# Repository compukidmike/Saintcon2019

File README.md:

# Saintcon 2019 Enigma Badge

## About the Badge
There is a writeup available at https://mkfactor.com/?p=100

There is also a video of my badge talk at Saintcon https://www.youtube.com/watch?v=MAhJ2W_oN14

## Completing the Badge Challenge
Since you probably don't have 26 badges and a Hut 6 "teleprinter" at your house, it will be difficult to complete the challenge. I have created a modified version of the badge firmware that will allow you to complete the challenge at home! You'll need to complete the steps for reprogramming your badge below. Once that's done, grab the Saintcon2019BadgeChallenge.pdf file from this repository. It has all the intercepted messages for you to decode. Be sure to decode them in order! Your badge should say "LEVELED UP" after successfully decoding a message. Good luck! If you get stuck, feel free to reach out on the SaintComms slack, or via twitter @compukidmike or even email compukidmike @ gmail.

## Reprogramming your badge
Note: This will completely erase the memory on your badge. Any progress in the challenge, as well as custom messages will be lost.

You will need the STM32CubeProgrammer software from https://www.st.com/en/development-tools/stm32cubeprog.html to reprogram your badge. It's cross-platform, though I've only tested it on Windows 10. Unfortunately ST requires you to create a login to download software :(

You'll also need the 2 hex files called Saintcon2019.hex and fpga.hex from this repository as well as a micro USB cable and one of the plugboard jumper wires from your badge.

Programming Steps:
1. Turn off the badge.
2. Connect the 2 TEST pins on your badge using the jumper (On the bottom-right side of your badge). If you haven't soldered that connector, you can put the jumper in from the back and hold it.
3. Connect the badge to your computer using a micro USB cable.
4. Turn on the badge. It will boot into DFU (Device Firmware Upgrade) mode.
5. From the STM32CubeProgrammer application, select USB from the drop-down menu at the top-right.
6. If you don't see anything next to "Serial number", click the little refresh button.
7. Click the green "Connect" button in the top-right corner. It should now say "Connected" above that button.
8. Click the Eraser button on the bottom-left corner (right above the question mark) and click OK to erase the badge memory. This is required for the new program to run correctly as there were many changes made to the way the internal EEPROM is organized.
9. Now click the "+" tab next to Device Memory and select "Open file". Choose one of the hex files you downloaded earlier. Now do the same for the other hex file.
10. With one of the hex file tabs selected, click the blue Download button. This will load the file onto your badge. Now do the same for the other hex file tab.
11. Remove the jumper and turn it off and back on. The first time you turn it on, it will go into a testing mode, where all the LEDs are turned on white. This is normal. Simply press each keyboard button until all the lampboard lights are off. It will say "TEST DONE". Turn it off and back on, and you are finished programming your badge. Enjoy!

## Editing Badge Code
The badge code can be found in the Firmware folder. It was written using the STM32CubeIDE. It's cross-platform and works reasonably well. You'll need an ST-Link V2 USB adapter to program and debug your badge. They can be had for ~$10 from Amazon or even less from Aliexpress if you're willing to wait for shipping.
The IDE can be downloaded from ST here: https://www.st.com/en/development-tools/stm32cubeide.html

The FPGA code was written using Icestudio https://icestudio.io/ It's a cross-platform IDE for Lattice ICE40 FPGAs

The FPGA code is in SaintconFPGA.ice

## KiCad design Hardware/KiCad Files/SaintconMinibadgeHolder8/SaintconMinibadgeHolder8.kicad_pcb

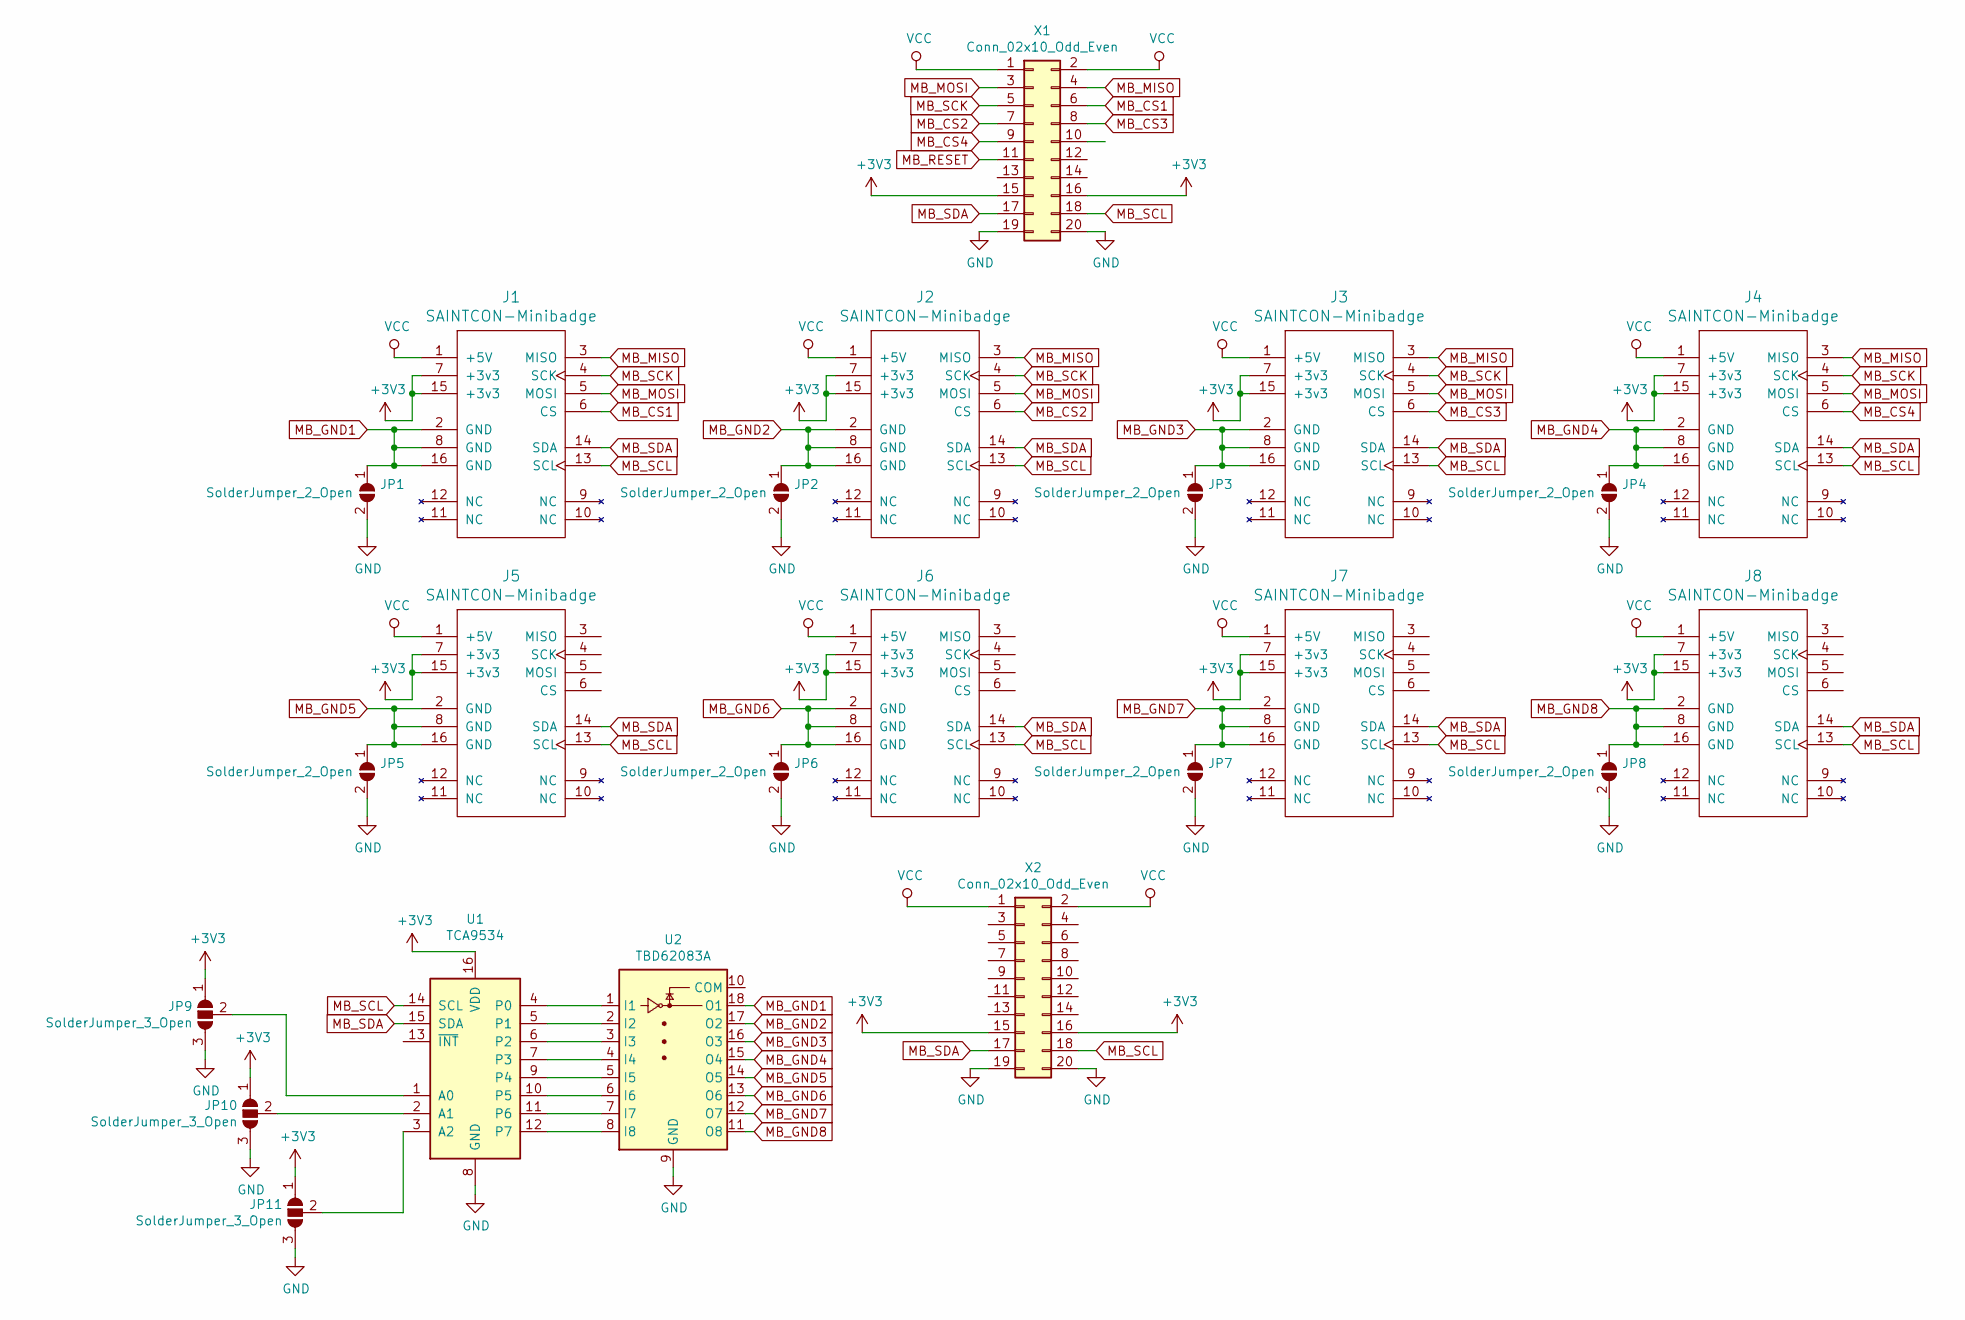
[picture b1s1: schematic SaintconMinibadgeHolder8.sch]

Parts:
J1, J2, J3, J4, J5, J6, J7, J8: SAINTCON-Minibadge; SAINTCON-Minibadge-Shiny
JP1, JP2, JP3, JP4, JP5, JP6, JP7, JP8: SolderJumper_2_Open; PAD-JUMPER-2-NO_YES_SILK
JP9, JP10, JP11: SolderJumper_3_Open; PAD-JUMPER-3-NO_YES_SILK
U1: TCA9534; SOIC-16W_7.5x10.3mm_Pitch1.27mm
U2: TBD62083A; SOIC-18W_7.5x11.6mm_Pitch1.27mm
X1, X2: Conn_02x10_Odd_Even; Pin_Header_Straight_2x10_Pitch2.54mm

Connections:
+3V3: J1.7 (+3v3), J1.15 (+3v3), J2.7 (+3v3), J2.15 (+3v3), J3.7 (+3v3), J3.15 (+3v3), J4.7 (+3v3), J4.15 (+3v3), J5.7 (+3v3), J5.15 (+3v3), J6.7 (+3v3), J6.15 (+3v3), J7.7 (+3v3), J7.15 (+3v3), J8.7 (+3v3), J8.15 (+3v3), JP9.1 (A), JP10.1 (A), JP11.1 (A), U1.16 (VDD), X1.15, X1.16, X2.15, X2.16
GND: JP1.2 (B), JP2.2 (B), JP3.2 (B), JP4.2 (B), JP5.2 (B), JP6.2 (B), JP7.2 (B), JP8.2 (B), JP9.3 (B), JP10.3 (B), JP11.3 (B), U1.8 (GND), U2.9 (GND), X1.19, X1.20, X2.19, X2.20
MB_CS1: J1.6 (CS), X1.6
MB_CS2: J2.6 (CS), X1.7
MB_CS3: J3.6 (CS), X1.8
MB_CS4: J4.6 (CS), X1.9
MB_GND1: J1.2 (GND), J1.8 (GND), J1.16 (GND), JP1.1 (A), U2.18 (O1)
MB_GND2: J2.2 (GND), J2.8 (GND), J2.16 (GND), JP2.1 (A), U2.17 (O2)
MB_GND3: J3.2 (GND), J3.8 (GND), J3.16 (GND), JP3.1 (A), U2.16 (O3)
MB_GND4: J4.2 (GND), J4.8 (GND), J4.16 (GND), JP4.1 (A), U2.15 (O4)
MB_GND5: J5.2 (GND), J5.8 (GND), J5.16 (GND), JP5.1 (A), U2.14 (O5)
MB_GND6: J6.2 (GND), J6.8 (GND), J6.16 (GND), JP6.1 (A), U2.13 (O6)
MB_GND7: J7.2 (GND), J7.8 (GND), J7.16 (GND), JP7.1 (A), U2.12 (O7)
MB_GND8: J8.2 (GND), J8.8 (GND), J8.16 (GND), JP8.1 (A), U2.11 (O8)
MB_MISO: J1.3 (MISO), J2.3 (MISO), J3.3 (MISO), J4.3 (MISO), X1.4
MB_MOSI: J1.5 (MOSI), J2.5 (MOSI), J3.5 (MOSI), J4.5 (MOSI), X1.3
MB_RESET: X1.11
MB_SCK: J1.4 (SCK), J2.4 (SCK), J3.4 (SCK), J4.4 (SCK), X1.5
MB_SCL: J1.13 (SCL), J2.13 (SCL), J3.13 (SCL), J4.13 (SCL), J5.13 (SCL), J6.13 (SCL), J7.13 (SCL), J8.13 (SCL), U1.14 (SCL), X1.18, X2.18
MB_SDA: J1.14 (SDA), J2.14 (SDA), J3.14 (SDA), J4.14 (SDA), J5.14 (SDA), J6.14 (SDA), J7.14 (SDA), J8.14 (SDA), U1.15 (SDA), X1.17, X2.17
unnamed: JP9.2 (C), U1.1 (A0)
unnamed: JP10.2 (C), U1.2 (A1)
unnamed: JP11.2 (C), U1.3 (A2)
unnamed: U1.4 (P0), U2.1 (I1)
unnamed: U1.5 (P1), U2.2 (I2)
unnamed: U1.6 (P2), U2.3 (I3)
unnamed: U1.7 (P3), U2.4 (I4)
unnamed: U1.9 (P4), U2.5 (I5)
unnamed: U1.10 (P5), U2.6 (I6)
unnamed: U1.11 (P6), U2.7 (I7)
unnamed: U1.12 (P7), U2.8 (I8)
VCC: J1.1 (+5V), J2.1 (+5V), J3.1 (+5V), J4.1 (+5V), J5.1 (+5V), J6.1 (+5V), J7.1 (+5V), J8.1 (+5V), X1.1, X1.2, X2.1, X2.2

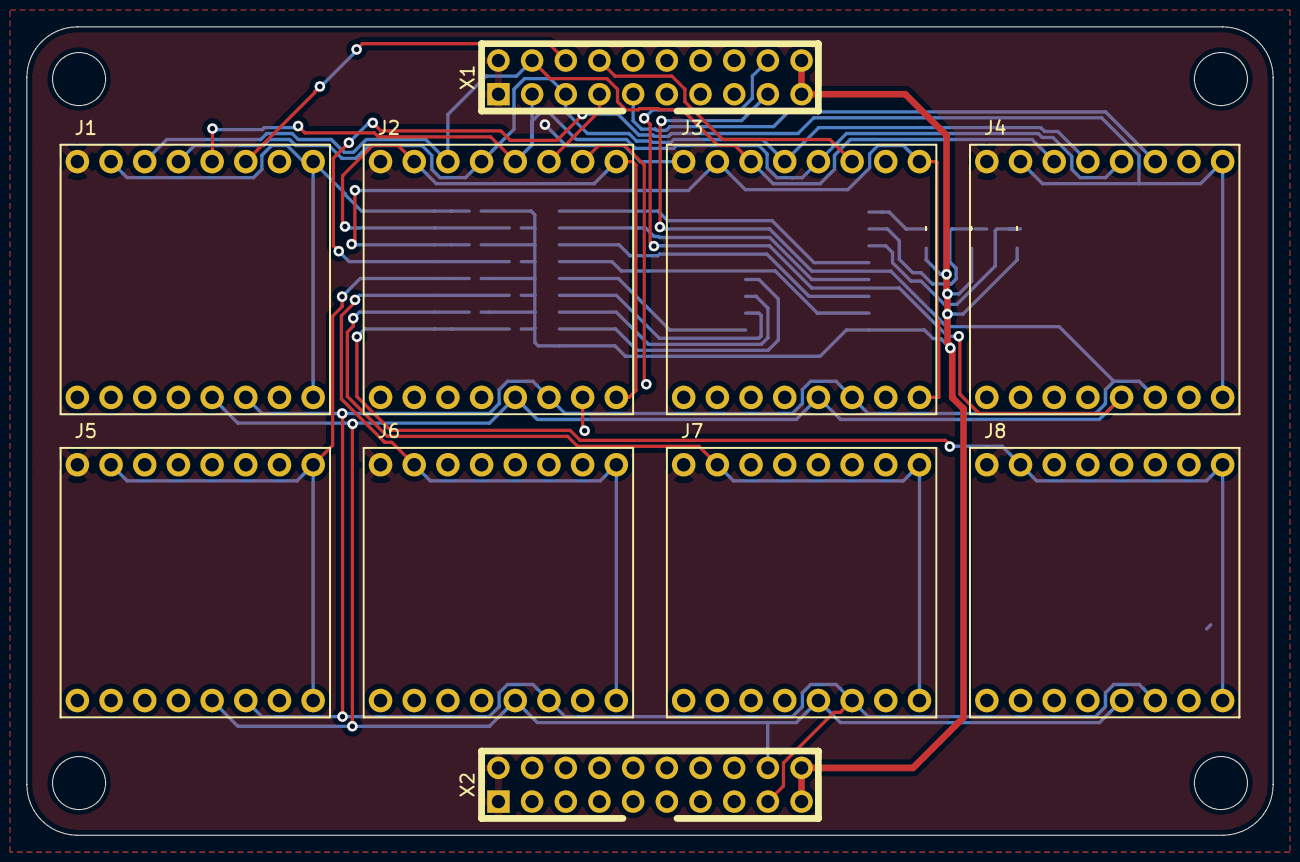
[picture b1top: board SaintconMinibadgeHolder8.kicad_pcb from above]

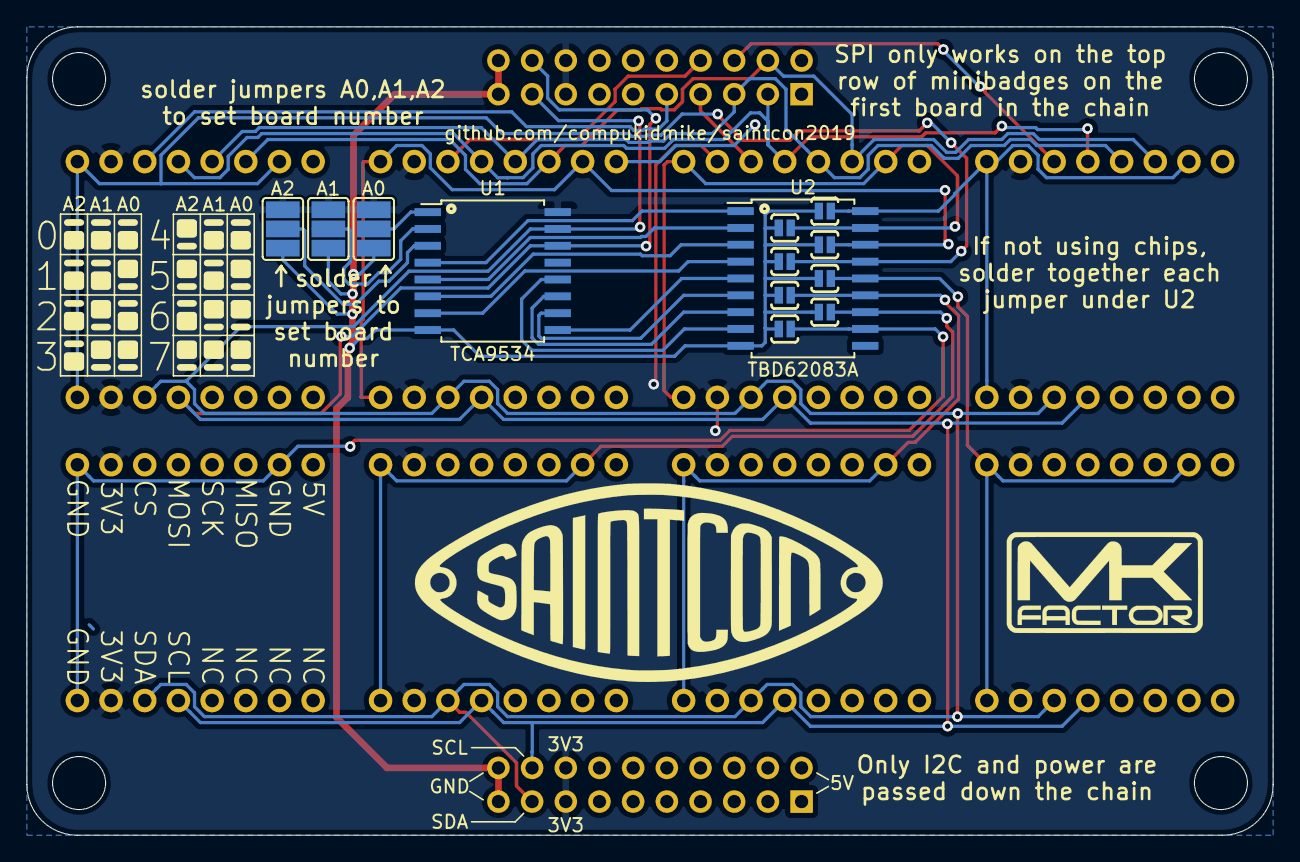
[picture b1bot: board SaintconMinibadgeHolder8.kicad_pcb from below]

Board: 2 copper layers, 94.0 x 61.0 mm, 24 parts (14 on the bottom side), 31 nets.

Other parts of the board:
Ref**: Val**; drawing

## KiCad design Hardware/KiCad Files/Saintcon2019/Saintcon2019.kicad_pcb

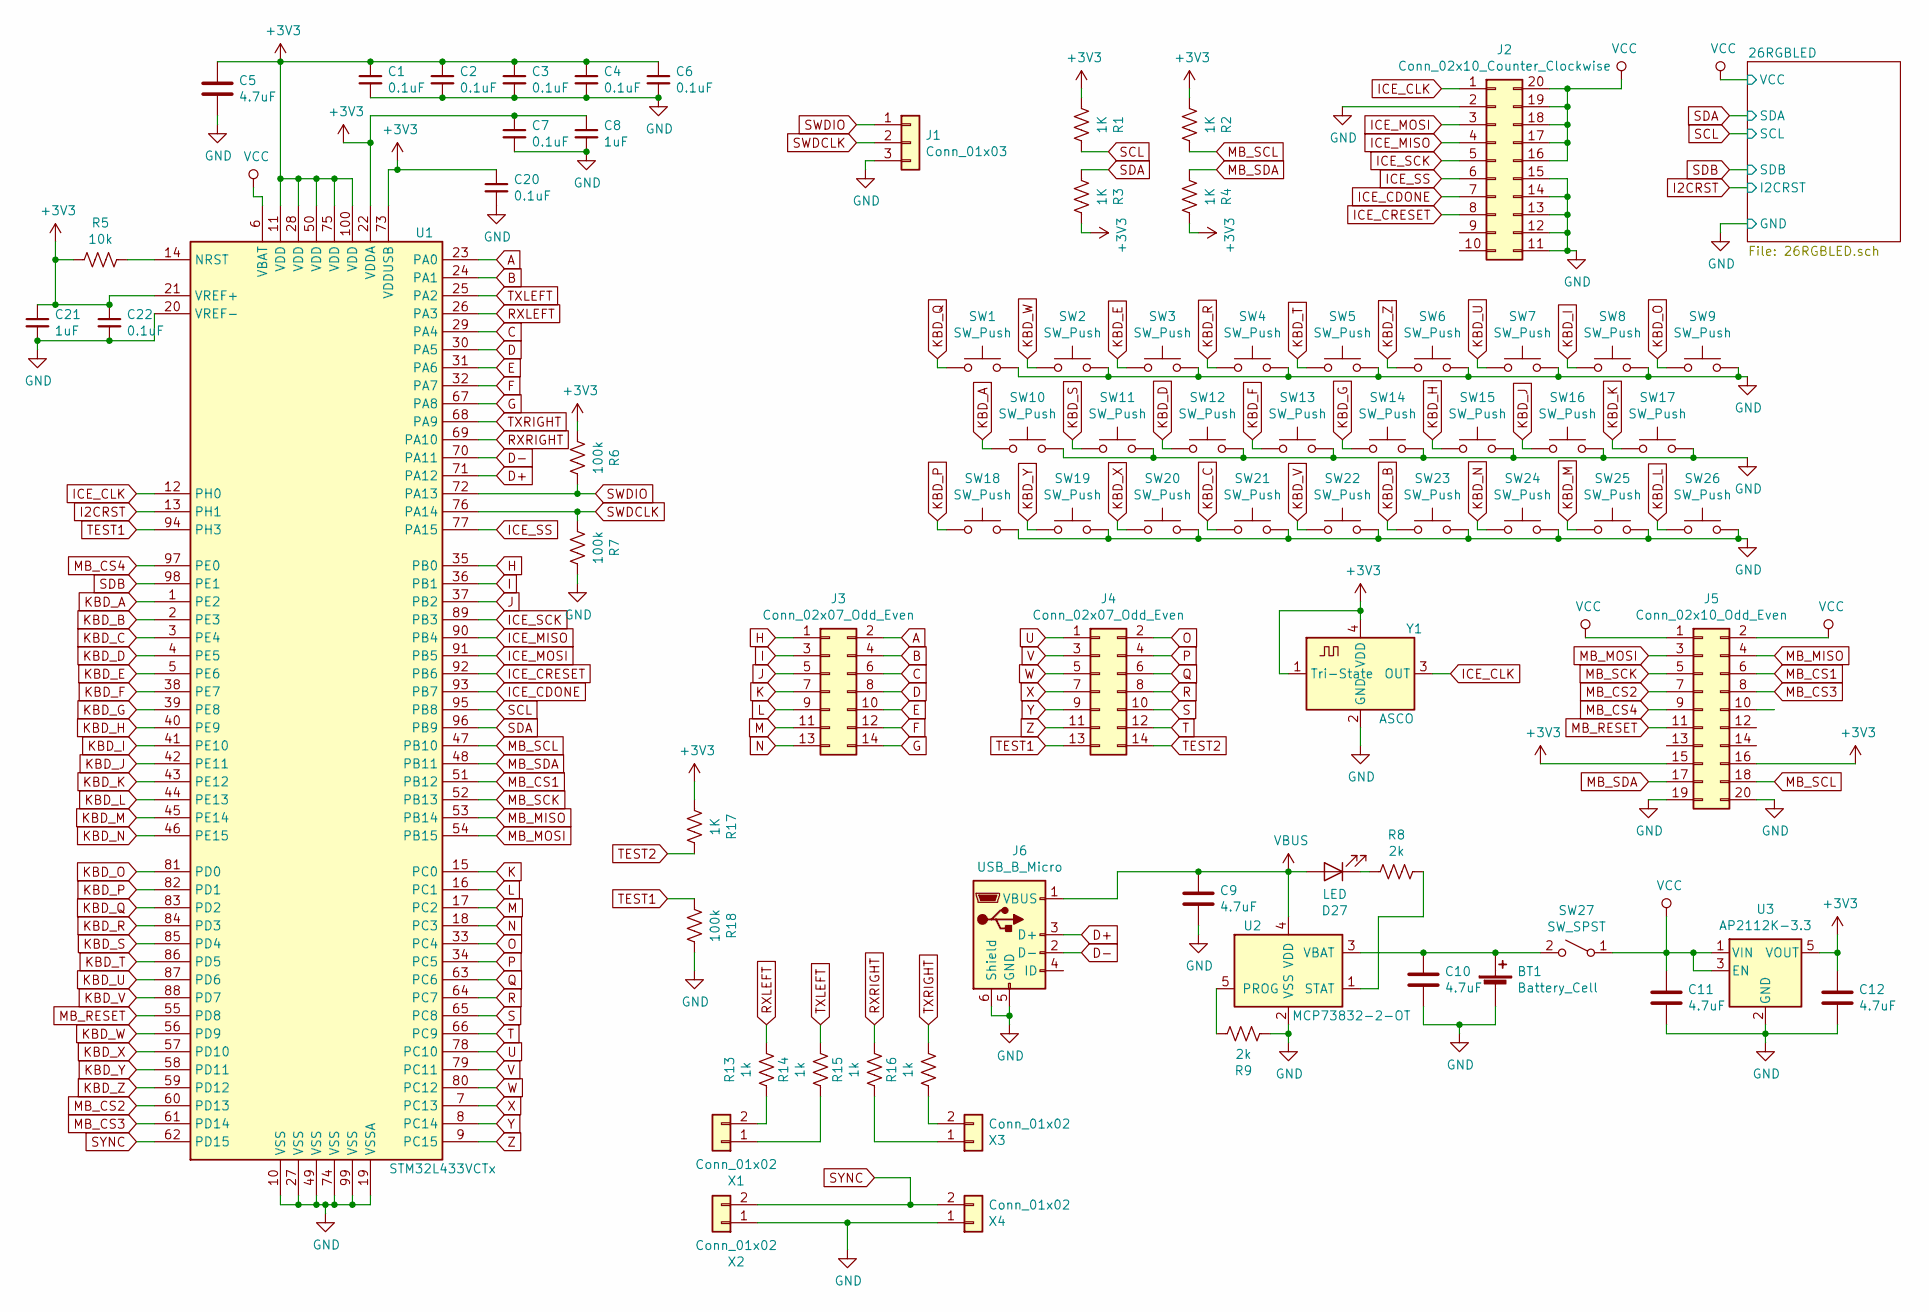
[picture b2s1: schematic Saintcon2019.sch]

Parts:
BT1: Battery_Cell; JST-2-SMD
C1, C2, C3, C4, C6, C7, C20, C22: 0.1uF; C_0603
C5, C9, C10, C11, C12: 4.7uF; C_0603
C8, C21: 1uF; C_0603
D27: LED; LED_0603
J1: Conn_01x03; 1X03
J2: Conn_02x10_Counter_Clockwise; BergStak_20Pin_0.5mm_Female_5.3mm
J3, J4: Conn_02x07_Odd_Even; Pin_Header_Straight_2x07_Pitch2.54mm
J5: Conn_02x10_Odd_Even; Pin_Header_Straight_2x10_Pitch2.54mm
J6: USB_B_Micro; 10118192-0002LF
R1, R2, R3, R4, R17: 1K; R_0603
R5: 10k; R_0603
R6, R7, R18: 100k; R_0603
R8, R9: 2k; R_0603
R13, R14, R15, R16: 1k; R_0603
SW1, SW2, SW3, SW4, SW5, SW6, SW7, SW8, SW9, SW10, SW11, SW12, SW13, SW14, SW15, SW16, SW17, SW18, SW19, SW20, SW21, SW22, SW23, SW24, SW25, SW26: SW_Push; TACT_6MM_SMD_SQUARE_TOP
SW27: SW_SPST; JS102011SAQN
U1: STM32L433VCTx; LQFP-100_14x14mm_Pitch0.5mm
U2: MCP73832-2-OT; SOT-23-5
U3: AP2112K-3.3; SOT-23-5
X1, X2: Conn_01x02; JST-LEB-2POS-FEMALE
X3, X4: Conn_01x02; JST-LEB-2POS-MALE
Y1: ASCO; ESC-2520MV

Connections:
+3V3: C1.1, C2.1, C3.1, C4.1, C5.1, C6.1, C7.1, C8.1, C12.1, C20.1, C21.1, C22.1, J5.15, J5.16, R1.2, R2.2, R3.1, R4.1, R5.2, R6.2, R17.2, U1.11 (VDD), U1.21 (VREF+), U1.22 (VDDA), U1.28 (VDD), U1.50 (VDD), U1.73 (VDDUSB), U1.75 (VDD), U1.100 (VDD), U3.5 (VOUT), Y1.1 (Tri-State), Y1.4 (VDD)
A: J3.2, U1.23 (PA0)
B: J3.4, U1.24 (PA1)
C: J3.6, U1.29 (PA4)
D: J3.8, U1.30 (PA5)
D+: J6.3 (D+), U1.71 (PA12)
D-: J6.2 (D-), U1.70 (PA11)
E: J3.10, U1.31 (PA6)
F: J3.12, U1.32 (PA7)
G: J3.14, U1.67 (PA8)
GND: BT1.2 (-), C1.2, C2.2, C3.2, C4.2, C5.2, C6.2, C7.2, C8.2, C9.2, C10.2, C11.2, C12.2, C20.2, C21.2, C22.2, J1.3, J2.2, J2.11, J2.12, J2.13, J2.14, J2.15, J5.19, J5.20, J6.5 (GND), J6.6 (Shield), R7.1, R9.2, R18.1, SW1.2, SW2.2, SW3.2, SW4.2, SW5.2, SW6.2, SW7.2, SW8.2, SW9.2, SW10.2, SW11.2, SW12.2, SW13.2, SW14.2, SW15.2, SW16.2, SW17.2, SW18.2, SW19.2, SW20.2, SW21.2, SW22.2, SW23.2, SW24.2, SW25.2, SW26.2, U1.10 (VSS), U1.19 (VSSA), U1.20 (VREF-), U1.27 (VSS), U1.49 (VSS), U1.74 (VSS), U1.99 (VSS), U2.2 (VSS), U3.2 (GND), X2.1, X4.1, Y1.2 (GND); also elsewhere on the board
H: J3.1, U1.35 (PB0)
I: J3.3, U1.36 (PB1)
I2CRST: U1.13 (PH1); also elsewhere on the board
ICE_CDONE: J2.7, U1.93 (PB7)
ICE_CLK: J2.1, U1.12 (PH0), Y1.3 (OUT)
ICE_CRESET: J2.8, U1.92 (PB6)
ICE_MISO: J2.4, U1.90 (PB4)
ICE_MOSI: J2.3, U1.91 (PB5)
ICE_SCK: J2.5, U1.89 (PB3)
ICE_SS: J2.6, U1.77 (PA15)
J: J3.5, U1.37 (PB2)
K: J3.7, U1.15 (PC0)
KBD_A: SW10.1, U1.1 (PE2)
KBD_B: SW23.1, U1.2 (PE3)
KBD_C: SW21.1, U1.3 (PE4)
KBD_D: SW12.1, U1.4 (PE5)
KBD_E: SW3.1, U1.5 (PE6)
KBD_F: SW13.1, U1.38 (PE7)
KBD_G: SW14.1, U1.39 (PE8)
KBD_H: SW15.1, U1.40 (PE9)
KBD_I: SW8.1, U1.41 (PE10)
KBD_J: SW16.1, U1.42 (PE11)
KBD_K: SW17.1, U1.43 (PE12)
KBD_L: SW26.1, U1.44 (PE13)
KBD_M: SW25.1, U1.45 (PE14)
KBD_N: SW24.1, U1.46 (PE15)
KBD_O: SW9.1, U1.81 (PD0)
KBD_P: SW18.1, U1.82 (PD1)
KBD_Q: SW1.1, U1.83 (PD2)
KBD_R: SW4.1, U1.84 (PD3)
KBD_S: SW11.1, U1.85 (PD4)
KBD_T: SW5.1, U1.86 (PD5)
KBD_U: SW7.1, U1.87 (PD6)
KBD_V: SW22.1, U1.88 (PD7)
KBD_W: SW2.1, U1.56 (PD9)
KBD_X: SW20.1, U1.57 (PD10)
KBD_Y: SW19.1, U1.58 (PD11)
KBD_Z: SW6.1, U1.59 (PD12)
L: J3.9, U1.16 (PC1)
M: J3.11, U1.17 (PC2)
MB_CS1: J5.6, U1.51 (PB12)
MB_CS2: J5.7, U1.60 (PD13)
MB_CS3: J5.8, U1.61 (PD14)
MB_CS4: J5.9, U1.97 (PE0)
MB_MISO: J5.4, U1.53 (PB14)
MB_MOSI: J5.3, U1.54 (PB15)
MB_RESET: J5.11, U1.55 (PD8)
MB_SCK: J5.5, U1.52 (PB13)
MB_SCL: J5.18, R2.1, U1.47 (PB10)
MB_SDA: J5.17, R4.2, U1.48 (PB11)
N: J3.13, U1.18 (PC3)
unnamed: BT1.1 (+), C10.1, SW27.2 (B), U2.3 (VBAT)
unnamed: D27.1 (K), R8.2
unnamed: R5.1, U1.14 (NRST)
unnamed: R8.1, U2.1 (STAT)
unnamed: R9.1, U2.5 (PROG)
unnamed: R13.2, X1.2
unnamed: R14.2, X1.1
unnamed: R15.2, X3.1
unnamed: R16.2, X3.2
O: J4.2, U1.33 (PC4)
P: J4.4, U1.34 (PC5)
Q: J4.6, U1.63 (PC6)
R: J4.8, U1.64 (PC7)
RXLEFT: R13.1, U1.26 (PA3)
RXRIGHT: R15.1, U1.69 (PA10)
S: J4.10, U1.65 (PC8)
SCL: R1.1, U1.95 (PB8); also elsewhere on the board
SDA: R3.2, U1.96 (PB9); also elsewhere on the board
SDB: U1.98 (PE1); also elsewhere on the board
SWDCLK: J1.2, R7.2, U1.76 (PA14)
SWDIO: J1.1, R6.1, U1.72 (PA13)
SYNC: U1.62 (PD15), X2.2, X4.2
T: J4.12, U1.66 (PC9)
TEST1: J4.13, R18.2, U1.94 (PH3)
TEST2: J4.14, R17.1
TXLEFT: R14.1, U1.25 (PA2)
TXRIGHT: R16.1, U1.68 (PA9)
U: J4.1, U1.78 (PC10)
V: J4.3, U1.79 (PC11)
VBUS: C9.1, D27.2 (A), J6.1 (VBUS), U2.4 (VDD)
VCC: C11.1, J2.16, J2.17, J2.18, J2.19, J2.20, J5.1, J5.2, SW27.1 (A), U1.6 (VBAT), U3.1 (VIN), U3.3 (EN); also elsewhere on the board
W: J4.5, U1.80 (PC12)
X: J4.7, U1.7 (PC13)
Y: J4.9, U1.8 (PC14)
Z: J4.11, U1.9 (PC15)

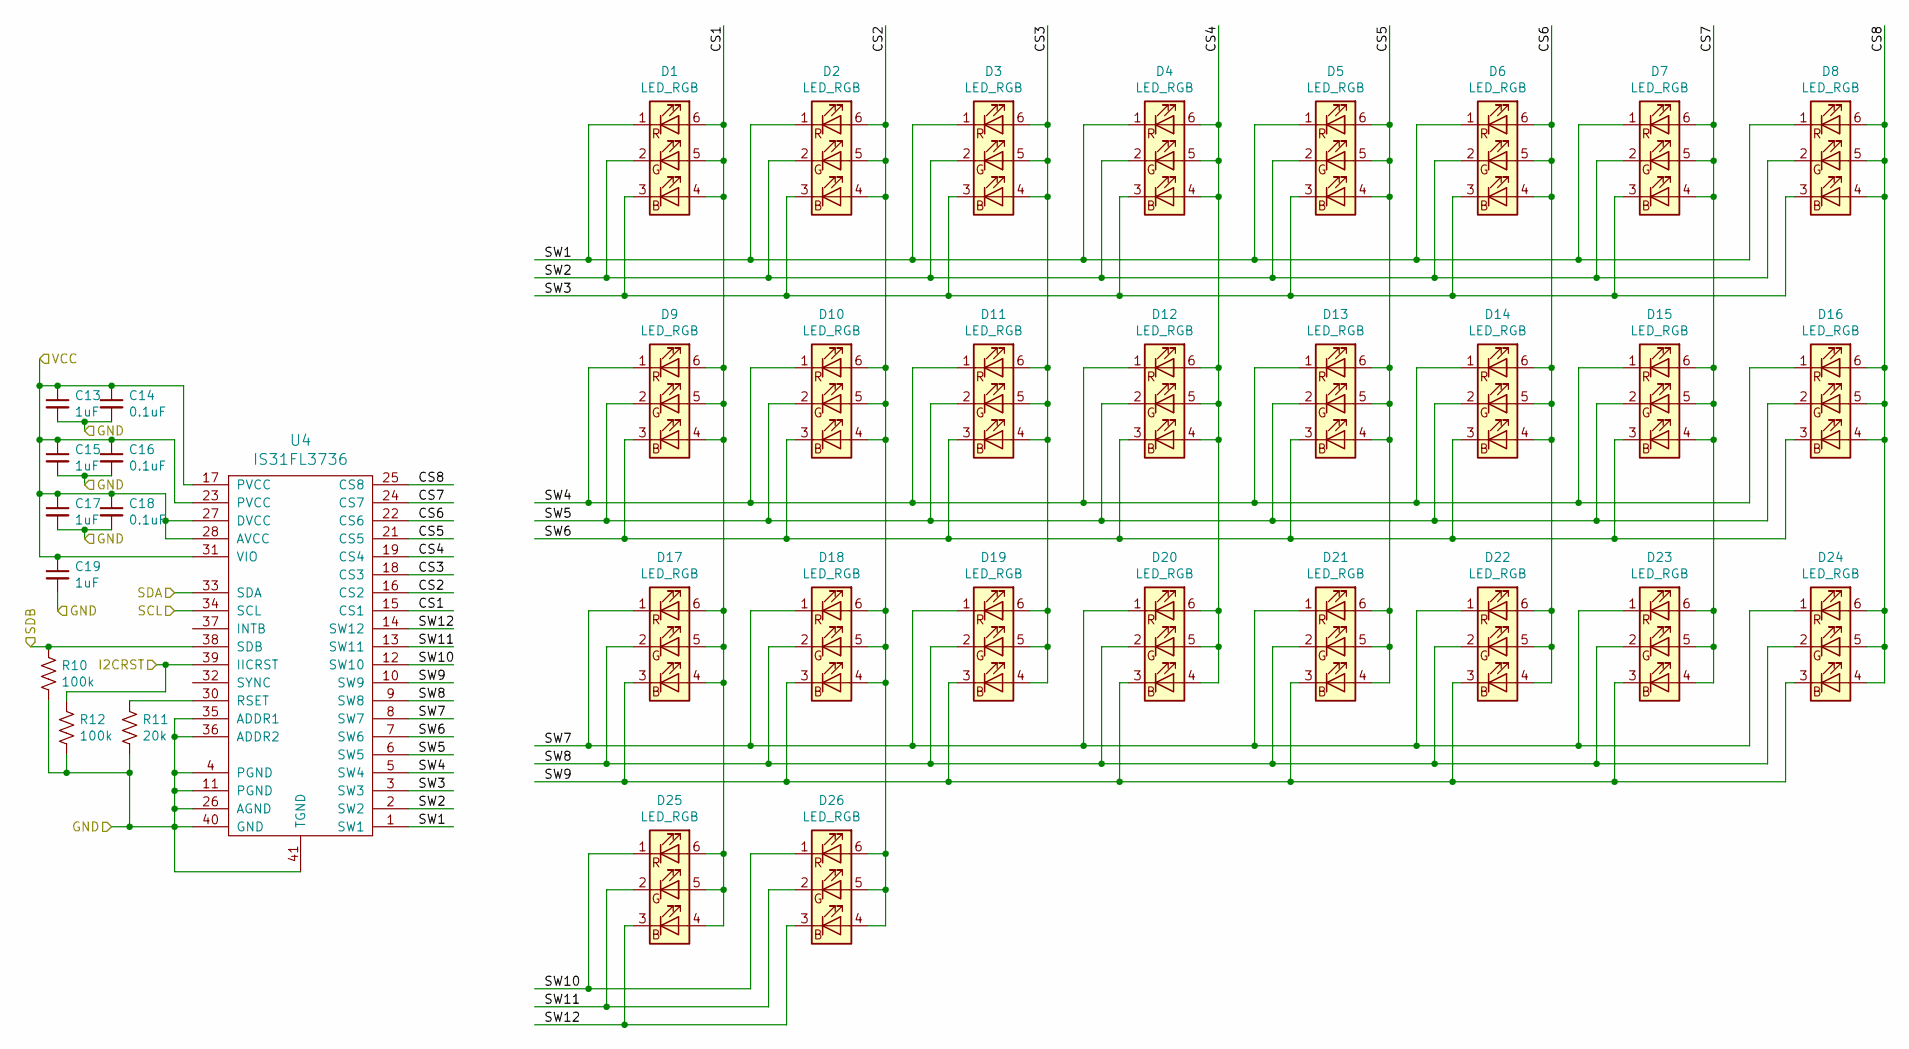
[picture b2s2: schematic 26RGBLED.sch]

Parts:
C13, C15, C17, C19: 1uF; C_0603
C14, C16, C18: 0.1uF; C_0603
D1, D2, D3, D4, D5, D6, D7, D8, D9, D10, D11, D12, D13, D14, D15, D16, D17, D18, D19, D20, D21, D22, D23, D24, D25, D26: LED_RGB; LED_RGB_5050-6
R10, R12: 100k; R_0603
R11: 20k; R_0603
U4: IS31FL3736; QFN-40-1EP_5x5mm_Pitch0.4mm

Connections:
/26RGBLED/CS1: D1.4 (BA), D1.5 (GA), D1.6 (RA), D9.4 (BA), D9.5 (GA), D9.6 (RA), D17.4 (BA), D17.5 (GA), D17.6 (RA), D25.4 (BA), D25.5 (GA), D25.6 (RA), U4.15 (CS1)
/26RGBLED/CS2: D2.4 (BA), D2.5 (GA), D2.6 (RA), D10.4 (BA), D10.5 (GA), D10.6 (RA), D18.4 (BA), D18.5 (GA), D18.6 (RA), D26.4 (BA), D26.5 (GA), D26.6 (RA), U4.16 (CS2)
/26RGBLED/CS3: D3.4 (BA), D3.5 (GA), D3.6 (RA), D11.4 (BA), D11.5 (GA), D11.6 (RA), D19.4 (BA), D19.5 (GA), D19.6 (RA), U4.18 (CS3)
/26RGBLED/CS4: D4.4 (BA), D4.5 (GA), D4.6 (RA), D12.4 (BA), D12.5 (GA), D12.6 (RA), D20.4 (BA), D20.5 (GA), D20.6 (RA), U4.19 (CS4)
/26RGBLED/CS5: D5.4 (BA), D5.5 (GA), D5.6 (RA), D13.4 (BA), D13.5 (GA), D13.6 (RA), D21.4 (BA), D21.5 (GA), D21.6 (RA), U4.21 (CS5)
/26RGBLED/CS6: D6.4 (BA), D6.5 (GA), D6.6 (RA), D14.4 (BA), D14.5 (GA), D14.6 (RA), D22.4 (BA), D22.5 (GA), D22.6 (RA), U4.22 (CS6)
/26RGBLED/CS7: D7.4 (BA), D7.5 (GA), D7.6 (RA), D15.4 (BA), D15.5 (GA), D15.6 (RA), D23.4 (BA), D23.5 (GA), D23.6 (RA), U4.24 (CS7)
/26RGBLED/CS8: D8.4 (BA), D8.5 (GA), D8.6 (RA), D16.4 (BA), D16.5 (GA), D16.6 (RA), D24.4 (BA), D24.5 (GA), D24.6 (RA), U4.25 (CS8)
/26RGBLED/SW1: D1.1 (RK), D2.1 (RK), D3.1 (RK), D4.1 (RK), D5.1 (RK), D6.1 (RK), D7.1 (RK), D8.1 (RK), U4.1 (SW1)
/26RGBLED/SW2: D1.2 (GK), D2.2 (GK), D3.2 (GK), D4.2 (GK), D5.2 (GK), D6.2 (GK), D7.2 (GK), D8.2 (GK), U4.2 (SW2)
/26RGBLED/SW3: D1.3 (BK), D2.3 (BK), D3.3 (BK), D4.3 (BK), D5.3 (BK), D6.3 (BK), D7.3 (BK), D8.3 (BK), U4.3 (SW3)
/26RGBLED/SW4: D9.1 (RK), D10.1 (RK), D11.1 (RK), D12.1 (RK), D13.1 (RK), D14.1 (RK), D15.1 (RK), D16.1 (RK), U4.5 (SW4)
/26RGBLED/SW5: D9.2 (GK), D10.2 (GK), D11.2 (GK), D12.2 (GK), D13.2 (GK), D14.2 (GK), D15.2 (GK), D16.2 (GK), U4.6 (SW5)
/26RGBLED/SW6: D9.3 (BK), D10.3 (BK), D11.3 (BK), D12.3 (BK), D13.3 (BK), D14.3 (BK), D15.3 (BK), D16.3 (BK), U4.7 (SW6)
/26RGBLED/SW7: D17.1 (RK), D18.1 (RK), D19.1 (RK), D20.1 (RK), D21.1 (RK), D22.1 (RK), D23.1 (RK), D24.1 (RK), U4.8 (SW7)
/26RGBLED/SW8: D17.2 (GK), D18.2 (GK), D19.2 (GK), D20.2 (GK), D21.2 (GK), D22.2 (GK), D23.2 (GK), D24.2 (GK), U4.9 (SW8)
/26RGBLED/SW9: D17.3 (BK), D18.3 (BK), D19.3 (BK), D20.3 (BK), D21.3 (BK), D22.3 (BK), D23.3 (BK), D24.3 (BK), U4.10 (SW9)
/26RGBLED/SW10: D25.1 (RK), D26.1 (RK), U4.12 (SW10)
/26RGBLED/SW11: D25.2 (GK), D26.2 (GK), U4.13 (SW11)
/26RGBLED/SW12: D25.3 (BK), D26.3 (BK), U4.14 (SW12)
GND: C13.2, C14.2, C15.2, C16.2, C17.2, C18.2, C19.2, R10.2, R11.2, R12.2, U4.4 (PGND), U4.11 (PGND), U4.26 (AGND), U4.35 (ADDR1), U4.36 (ADDR2), U4.40 (GND), U4.41 (TGND); also elsewhere on the board
I2CRST: R12.1, U4.39 (IICRST); also elsewhere on the board
unnamed: R11.1, U4.30 (RSET)
SCL: U4.34 (SCL); also elsewhere on the board
SDA: U4.33 (SDA); also elsewhere on the board
SDB: R10.1, U4.38 (SDB); also elsewhere on the board
VCC: C13.1, C14.1, C15.1, C16.1, C17.1, C18.1, C19.1, U4.17 (PVCC), U4.23 (PVCC), U4.27 (DVCC), U4.28 (AVCC), U4.31 (VIO); also elsewhere on the board

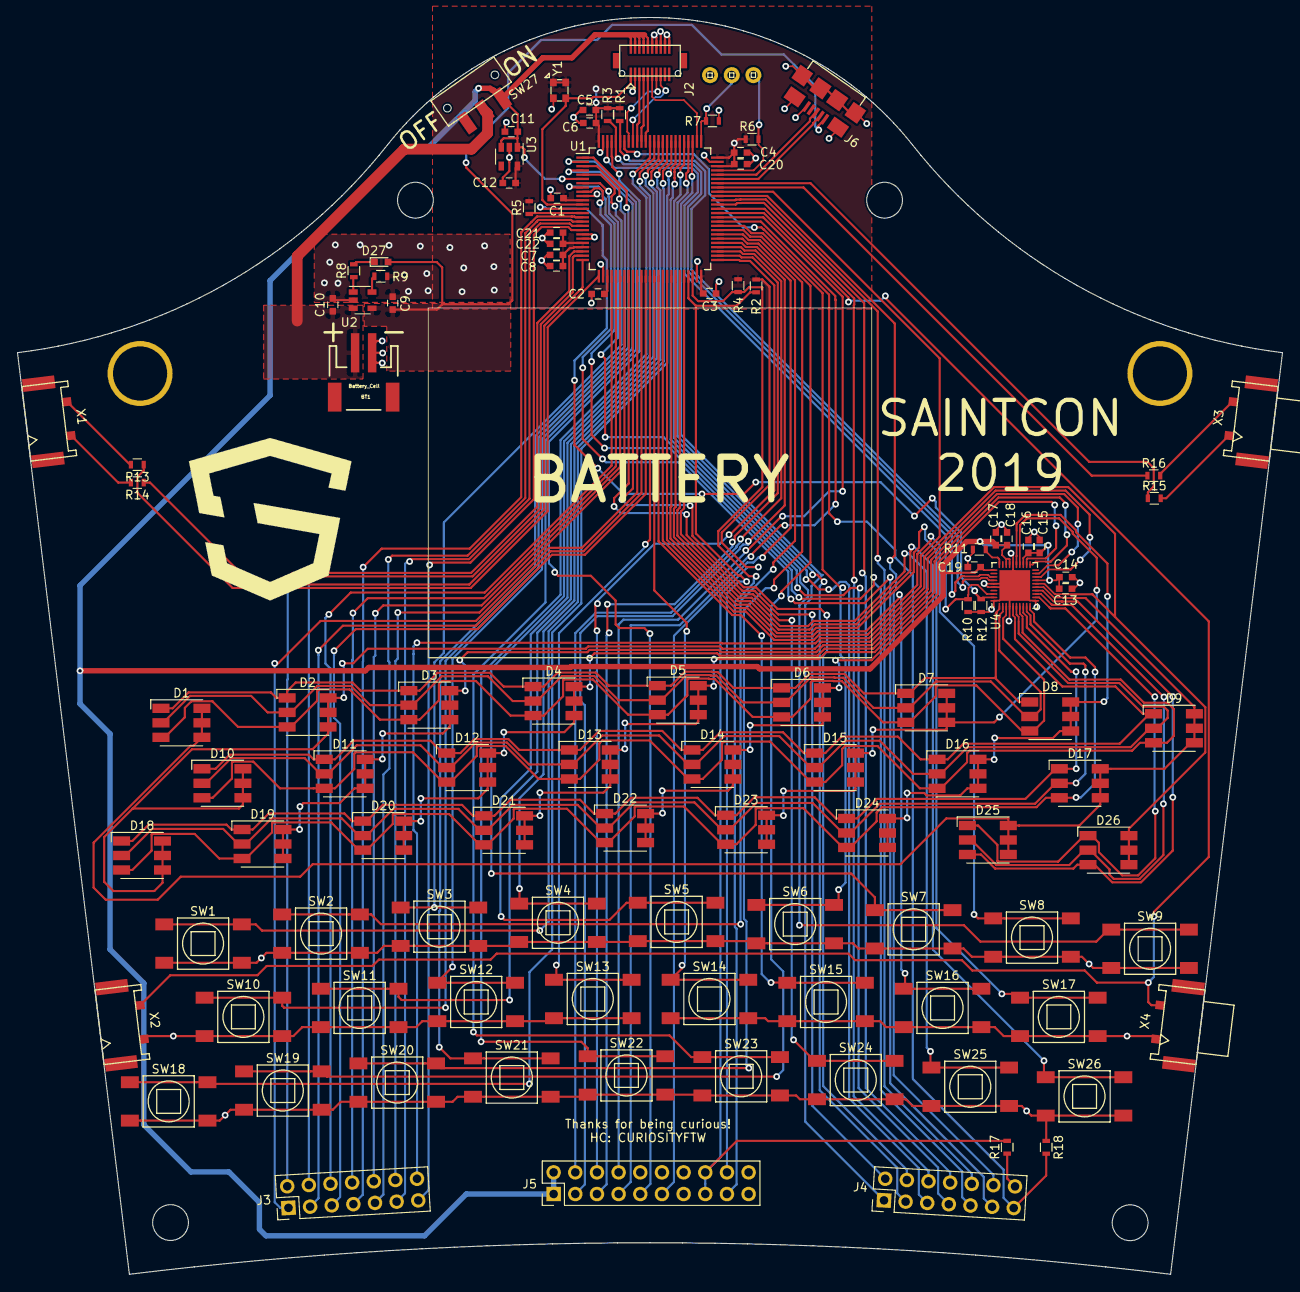
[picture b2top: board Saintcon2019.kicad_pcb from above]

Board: 2 copper layers, 148.3 x 147.3 mm, 112 parts (1 on the bottom side), 118 nets.

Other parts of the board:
Back: Val**; Saintcon2019BaseBoardArtwork
Ref**: Val**; Saintcon2019TopBoardArtwork2

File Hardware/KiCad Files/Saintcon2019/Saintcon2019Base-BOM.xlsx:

Item # | Ref Des | Qty | Manufacturer | Mfg Part # | Description / Value | Package | Type | Your Instructions / Notes
1.0 | BT1 | 1.0 | JST Sales America Inc. | S2B-PH-SM4-TB(LF)(SN) | CONN HEADER SMD R/A 2POS 2MM | 2-SMD | SMD
2.0 | C1, C2, C3, C4, C6, C7, C14, C16, C18, C20, C22 | 11.0 |  |  | CAPACITOR 0.1uF 0603 | 0603 | SMD
3.0 | C5, C9, C10, C11, C12 | 5.0 |  |  | CAPACITOR 4.7uF 0603 | 0603 | SMD
4.0 | C8, C13, C15, C17, C19, C21 | 6.0 |  |  | CAPACITOR 1uF 0603 | 0603 | SMD
5.0 | D1, D2, D3, D4, D5, D6, D7, D8, D9, D10, D11, D12, D13, D14, D15, D16, D17, D18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 | 26.0 | Varies | Varies | 5050 RGB LED | PLCC-6 (5050) | SMD | https://www.aliexpress.com/item/Led-Lamp-SMD-Led-Diode-RGB-L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
6.0 | D27 | 1.0 |  |  | LED RED 0603 | 0603 | SMD
7.0 | J1 | 1.0 | DNP | DNP | DNP
8.0 | J2 | 1.0 | Amphenol ICC (FCI) | 10132797-027100LF | CONN PLUG 20POS SMD GOLD | 20*0.5mm | SMD
9.0 | J3, J4 | 2.0 | DNP | DNP | DNP
10.0 | J5 | 1.0 | DNP | DNP | DNP
11.0 | J6 | 1.0 | Amphenol ICC (FCI) | 10118192-0002LF | CONN RCPT USB2.0 MICRO B SMD R/A | USB | SMD
12.0 | R1, R2, R3, R4 | 4.0 |  |  | RESISTOR 1k 0603 | 0603 | SMD
13.0 | R5, R13, R14, R15, R16, R17 | 6.0 |  |  | RESISTOR 10k 0603 | 0603 | SMD
14.0 | R6, R7, R10, R12 | 4.0 |  |  | RESISTOR 100k 0603 | 0603 | SMD
15.0 | R8, R9 | 2.0 |  |  | RESISTOR 2k 0603 | 0603 | SMD
16.0 | R11 | 1.0 |  |  | RESISTOR 20k 0603 | 0603 | SMD
17.0 | SW1, SW2, SW3, SW4, SW5, SW6, SW7, SW8, SW9, SW10, SW11, SW12, SW13, SW14, SW15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 | 26.0 | Varies | Varies | TACH SWITCH SQUARE HEAD 6x6MM | 4-SMD | SMD | https://www.aliexpress.com/item/32726480469.html?spm=2114.se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
18.0 | SW27 | 1.0 | C&K | JS102011SAQN | SWITCH SLIDE SPDT 300MA 6V | 3-SMD | SMD
19.0 | U1 | 1.0 | STMicroelectronics | STM32L433VCT6 | IC MCU 32BIT 256KB FLASH 100LQFP | 100LQFP | SMD
20.0 | U2 | 1.0 | Microchip Technology | MCP73832T-2ACI/OT | IC LI-ION/LI-POLY CTRLR SOT23-5 | SOT-23-5 | SMD
21.0 | U3 | 1.0 | Diodes Incorporated | AP2112K-3.3TRG1 | IC REG LINEAR 3.3V 600MA SOT25 | SOT-23-5 | SMD
22.0 | U4 | 1.0 | ISSI, Integrated Silicon Solution Inc | IS31FL3736-QFLS4-TR | IC LED DRVR LINEAR 45MA 40QFN | 40-QFN | SMD
23.0 | X1, X2 | 2.0 | JST Sales America Inc. | 02R-LEBSS-TB(LF)(SN) | CONN SSL RCPT 2POS 4MM SOLDER | 2-SMD | SMD
24.0 | X3, X4 | 2.0 | JST Sales America Inc. | 02P-LEBSS-TF(LF)(SN) | CONN SSL PLUG 2POS 4MM SOLDER | 2-SMD | SMD
25.0 | Y1 | 1.0 | ECS Inc. | ECS-2520MV-120-BN-TR | XTAL OSC XO 12.0000MHZ CMOS SMD | 4-SMD | SMD
